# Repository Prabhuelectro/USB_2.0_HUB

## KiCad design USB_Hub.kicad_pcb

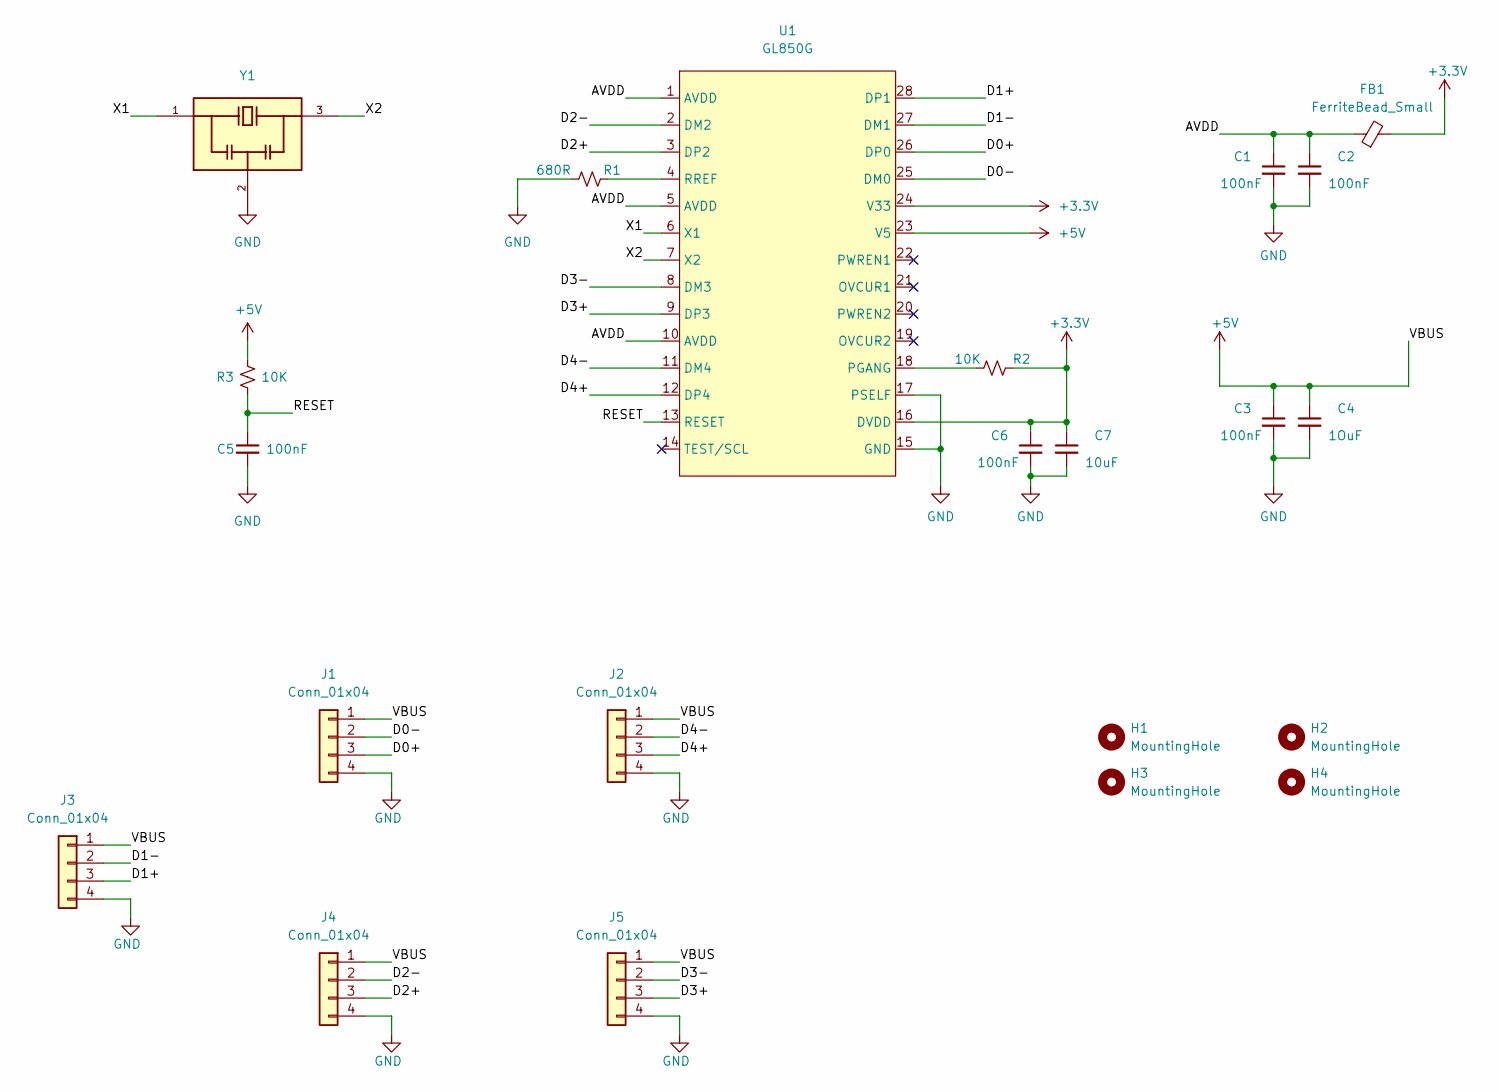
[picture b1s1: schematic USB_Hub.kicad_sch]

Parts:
C1, C2, C3, C5, C6: 100nF; C_0603_1608Metric
C4: 1OuF; C_0603_1608Metric
C7: 10uF; C_0603_1608Metric
FB1: FerriteBead_Small; L_0603_1608Metric
H1, H2, H3, H4: MountingHole; MountingHole_2.2mm_M2
J1, J2, J3, J4, J5: Conn_01x04; JST-4P_1.25mm
R1: 680R; R_0603_1608Metric
R2, R3: 10K; R_0603_1608Metric
U1: GL850G; SOIC-28
Y1: CSTNE12M0G55A000R0; Cera_Resona_12MHz-CSTNE12M0G55A000R0

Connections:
+3.3V: C6.1, C7.1, FB1.2, R2.1, U1.16 (DVDD), U1.24 (V33)
+5V: C3.1, C4.1, J1.1, J2.1, J3.1, J4.1, J5.1, R3.2, U1.23 (V5)
/AVDD: C1.1, C2.1, FB1.1, U1.1 (AVDD), U1.5 (AVDD), U1.10 (AVDD)
/D0+: J1.3, U1.26 (DP0)
/D0-: J1.2, U1.25 (DM0)
/D1+: J3.3, U1.28 (DP1)
/D1-: J3.2, U1.27 (DM1)
/D2+: J4.3, U1.3 (DP2)
/D2-: J4.2, U1.2 (DM2)
/D3+: J5.3, U1.9 (DP3)
/D3-: J5.2, U1.8 (DM3)
/D4+: J2.3, U1.12 (DP4)
/D4-: J2.2, U1.11 (DM4)
/RESET: C5.1, R3.1, U1.13 (RESET)
/X1: U1.6 (X1), Y1.1
/X2: U1.7 (X2), Y1.3
GND: C1.2, C2.2, C3.2, C4.2, C5.2, C6.2, C7.2, J1.4, J2.4, J3.4, J4.4, J5.4, R1.1, U1.15 (GND), U1.17 (PSELF), Y1.2
unnamed: R1.2, U1.4 (RREF)
unnamed: R2.2, U1.18 (PGANG)

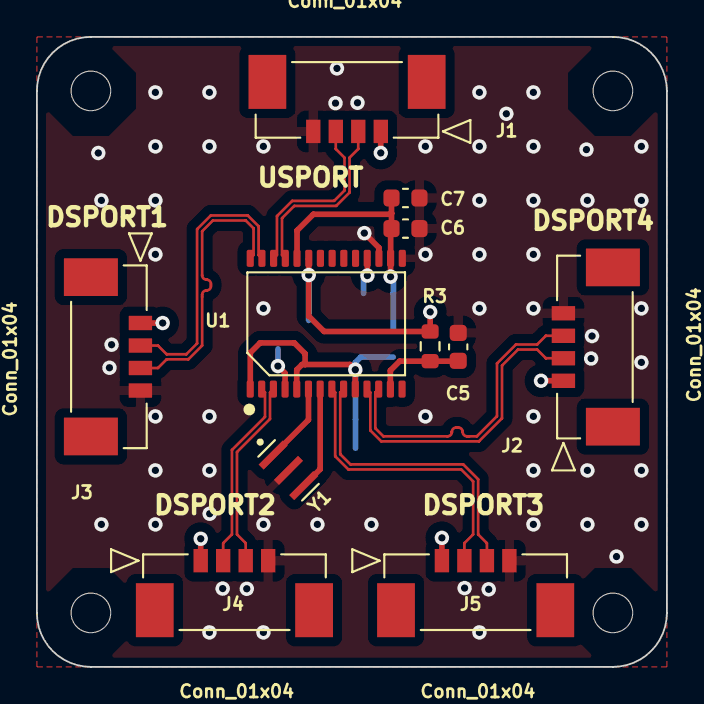
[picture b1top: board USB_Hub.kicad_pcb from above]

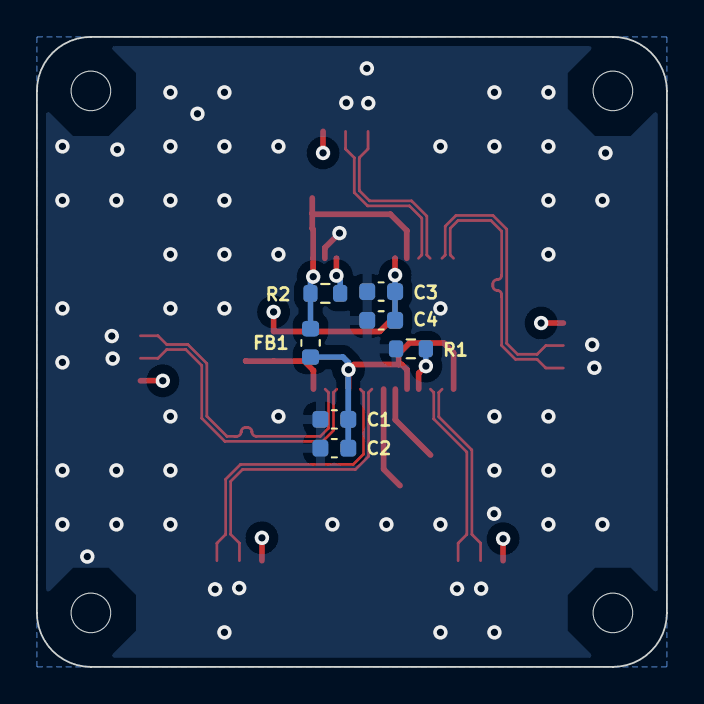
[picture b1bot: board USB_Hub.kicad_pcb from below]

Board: 4 copper layers, 35.0 x 35.0 mm, 22 parts (7 on the bottom side), 19 nets.

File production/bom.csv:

Designator,Footprint,Quantity,Value,LCSC Part #
"C1, C2, C3, C5, C6",C_0603_1608Metric,5,100nF,
C4,C_0603_1608Metric,1,1OuF,
C7,C_0603_1608Metric,1,10uF,
FB1,L_0603_1608Metric,1,FerriteBead_Small,
"H1, H2, H3, H4",MountingHole_2.2mm_M2,4,MountingHole,
"J1, J2, J3, J4, J5",JST-4P_1.25mm,5,Conn_01x04,
R1,R_0603_1608Metric,1,680R,
"R2, R3",R_0603_1608Metric,2,10K,
U1,SOIC-28,1,GL850G,
Y1,Cera_Resona_12MHz-CSTNE12M0G55A000R0,1,CSTNE12M0G55A000R0,

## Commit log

2024-03-15 USB 2.0 Four Port HUB
